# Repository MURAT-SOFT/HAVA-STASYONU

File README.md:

HAVA İSTASYON CİHAZI  HG-1,HG-2,HG-3,HG-4,HG-4İ VE B (V.1.2)
1.TASARIM SOLIDWORKS 2018
2.DONANIM TASARIMI : DIPTRACE VEYA AUTODESK EAGLE v.2024
3.YAZILIM: CCS-C C DERLEYİCİ v.5.11 VE STM32 CUBE IDE 
--------------------------------------------------------
KULLANILAN SENSÖRLER:
1.BOSCH BME280
2.DHT22 VEYA DS18B20 VE LM335,TC77
3.ANAKART PIC16F877A,PIC18F452,PIC18F4550,STM32103CBT6,STM32F407ZGT6,MSP430 VE ARDUINO
4.VOLTAJ REGÜLATÖR + TRAFO: 220v-> 12v 
5.EKRAN 1.ST7735 1.8/ST7789 2.4 INÇ VEYA LCD 16x2 
--------------------------------------------------------

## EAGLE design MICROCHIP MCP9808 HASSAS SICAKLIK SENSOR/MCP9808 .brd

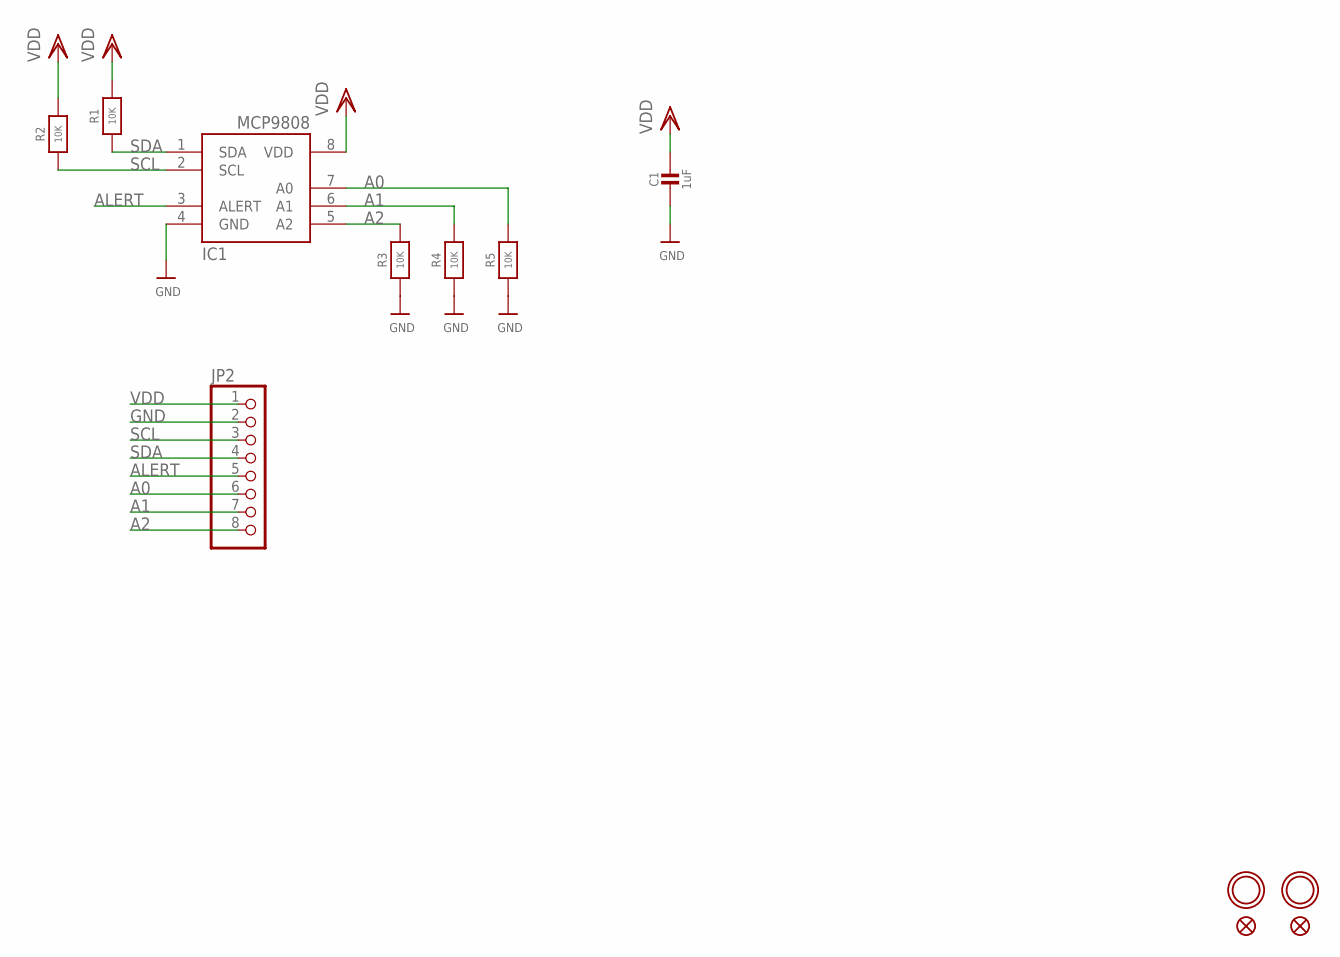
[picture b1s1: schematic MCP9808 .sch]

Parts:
C1: 1uF; _0805MP
FID1, FID2: FIDUCIAL""; FIDUCIAL_1MM
IC1: MCP9808-E/MS; MSOP8_0.65MM
JP2: HEADER-1X870MIL; 1X08_ROUND_70
R1, R2, R3, R4, R5: 10K; 0805-NO
U$3, U$5: MOUNTINGHOLE2.5; MOUNTINGHOLE_2.5_PLATED

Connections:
A0: IC1.7 (A0), JP2.6, R5.2
A1: IC1.6 (A1), JP2.7, R4.2
A2: IC1.5 (A2), JP2.8, R3.2
ALERT: IC1.3 (ALERT), JP2.5
GND: C1.2, IC1.4 (GND), JP2.2, R3.1, R4.1, R5.1
SCL: IC1.2 (SCL), JP2.3, R2.1
SDA: IC1.1 (SDA), JP2.4, R1.1
VDD: C1.1, IC1.8 (VDD), JP2.1, R1.2, R2.2

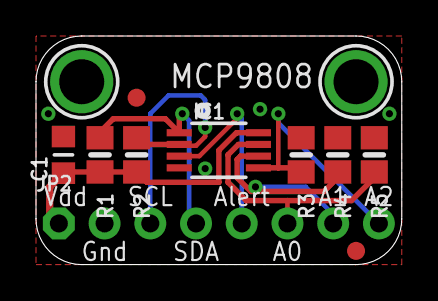
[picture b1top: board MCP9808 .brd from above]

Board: 2 copper layers, 20.3 x 12.7 mm, 12 parts (0 on the bottom side), 8 nets.

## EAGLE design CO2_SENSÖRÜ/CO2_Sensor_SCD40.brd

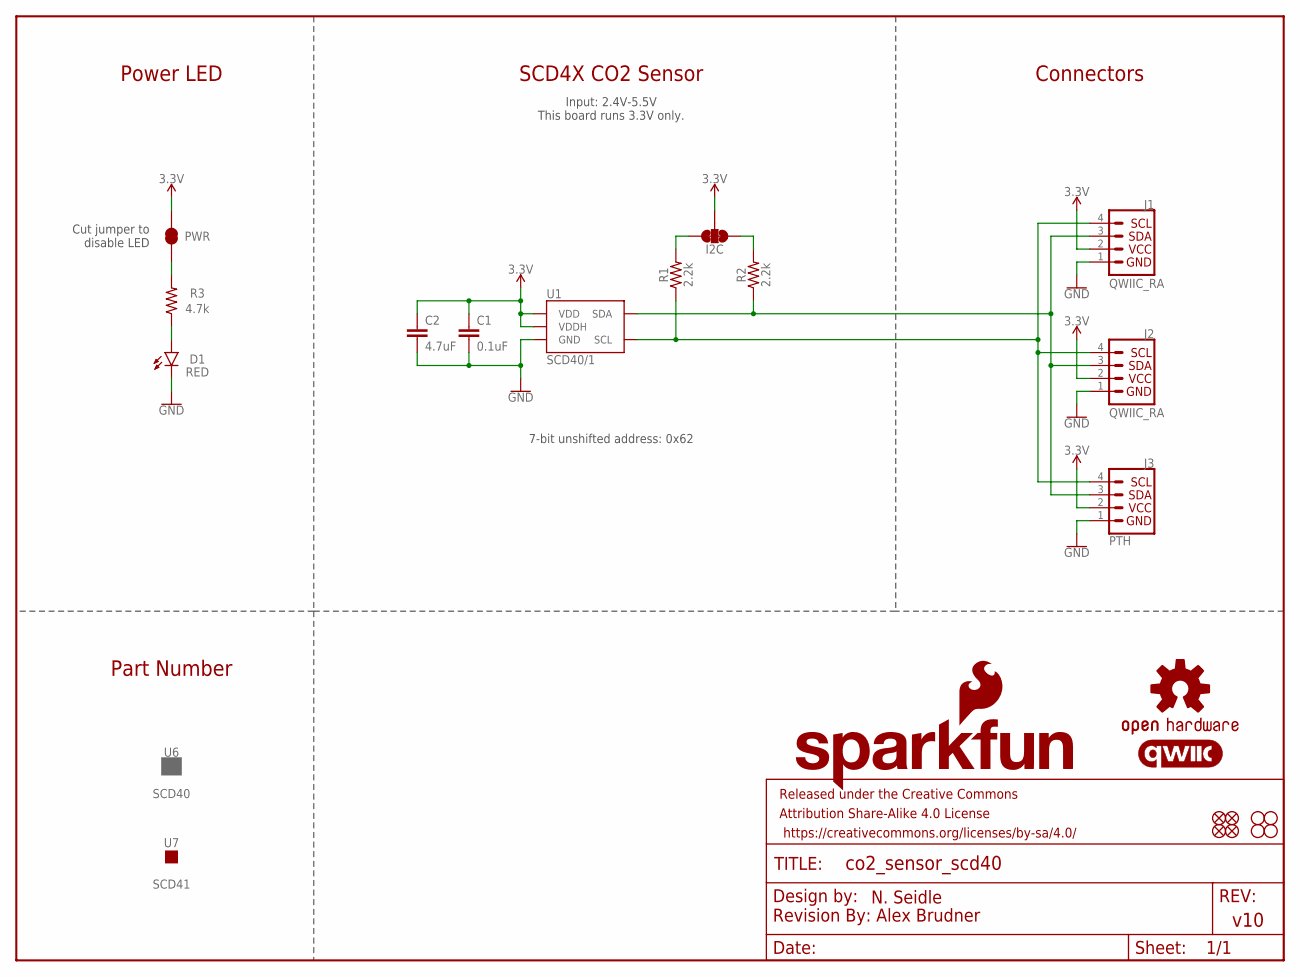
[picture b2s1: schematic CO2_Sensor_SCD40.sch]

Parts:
C1: 0.1uF; 0603
C2: 4.7uF; 0603
D1: RED; LED-0603
FD1, FD2, FD3, FD4: FIDUCIALUFIDUCIAL; FIDUCIAL-MICRO
FRAME1: FRAME-LETTER; CREATIVE_COMMONS
H1, H2, H3, H4: STAND-OFF
I2C: I2C; SMT-JUMPER_3_2-NC_TRACE_SILK
J1, J2: QWIIC_RA; JST04_1MM_RA
J3: PTH; 1X04_NO_SILK
LOGO1: QWIIC_LOGO_CONNECTOR; QWIIC_5.5MM
LOGO2: OSHW-LOGOS; OSHW-LOGO-S
LOGO3: SFE_LOGO_NAME_FLAMEBLANK; BLANK
PWR: PWR; SMT-JUMPER_2_NC_TRACE_SILK
R1, R2: 2.2k; 0603
R3: 4.7k; 0603
U1: SCD40/1; SCD4X
U6: SCD40; PRODUCT_IDENT_PASTE_NO-SILK
U7: SCD41; PRODUCT_IDENT_NO_NO-SILK

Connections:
3.3V: C1.1, C2.1, I2C.2, J1.2, J2.2, J3.2, PWR.2, U1.7 (VDD), U1.19 (VDDH)
GND: C1.2, C2.2, D1.C, J1.1, J2.1, J3.1, U1.6 (GND), U1.20 (GND), U1.CP (GND)
unnamed: I2C.1, R2.2
unnamed: I2C.3, R1.2
unnamed: PWR.1, R3.2
unnamed: D1.A, R3.1
SCL: J1.4, J2.4, J3.4, R1.1, U1.9 (SCL)
SDA: J1.3, J2.3, J3.3, R2.1, U1.10 (SDA)

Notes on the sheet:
Cut jumper to disable LED
SCD4X CO2 Sensor
Power LED
Connectors
Part Number
Input: 2.4V-5.5V This board runs 3.3V only.
7-bit unshifted address: 0x62

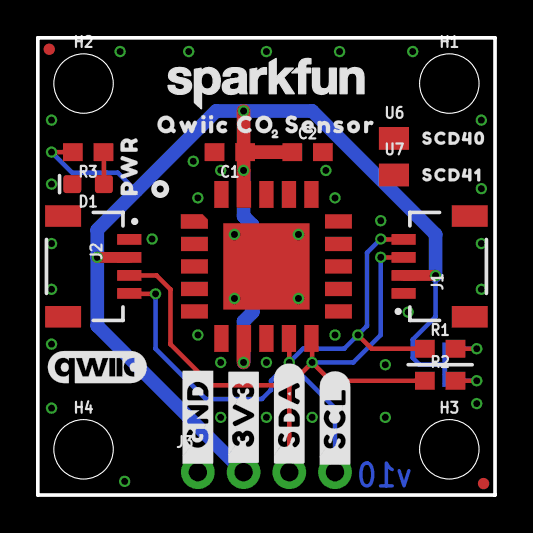
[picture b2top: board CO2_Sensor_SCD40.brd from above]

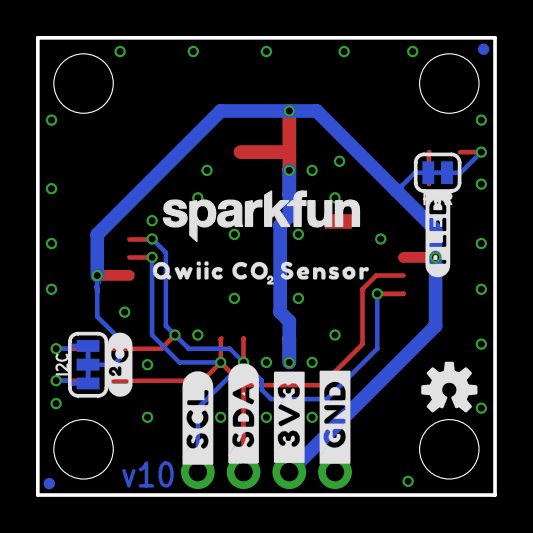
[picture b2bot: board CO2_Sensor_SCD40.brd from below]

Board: 2 copper layers, 25.4 x 25.4 mm, 49 parts (16 on the bottom side), 8 nets.

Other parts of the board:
U$1, U$18: #_GND#14
U$2, U$19: #_3V3#15
U$3, U$20: #_SDA#15
U$4, U$21: #_SCL#16
U$5, U$12: SFE_LOGO_NAME_.1
U$6: SCD414140404021
U$7: SCD40414140404022
U$8, U$13: QWIIC_CO0
U$9, U$14: SENSOR0
U$10, U$15: 20
U$11: SFE_LOGO_FLAME_STOP_.1
U$16: #PLED#21
U$17: #I�C#0
U$22: ORDERING_INSTRUCTIONS
U$23: PWR0

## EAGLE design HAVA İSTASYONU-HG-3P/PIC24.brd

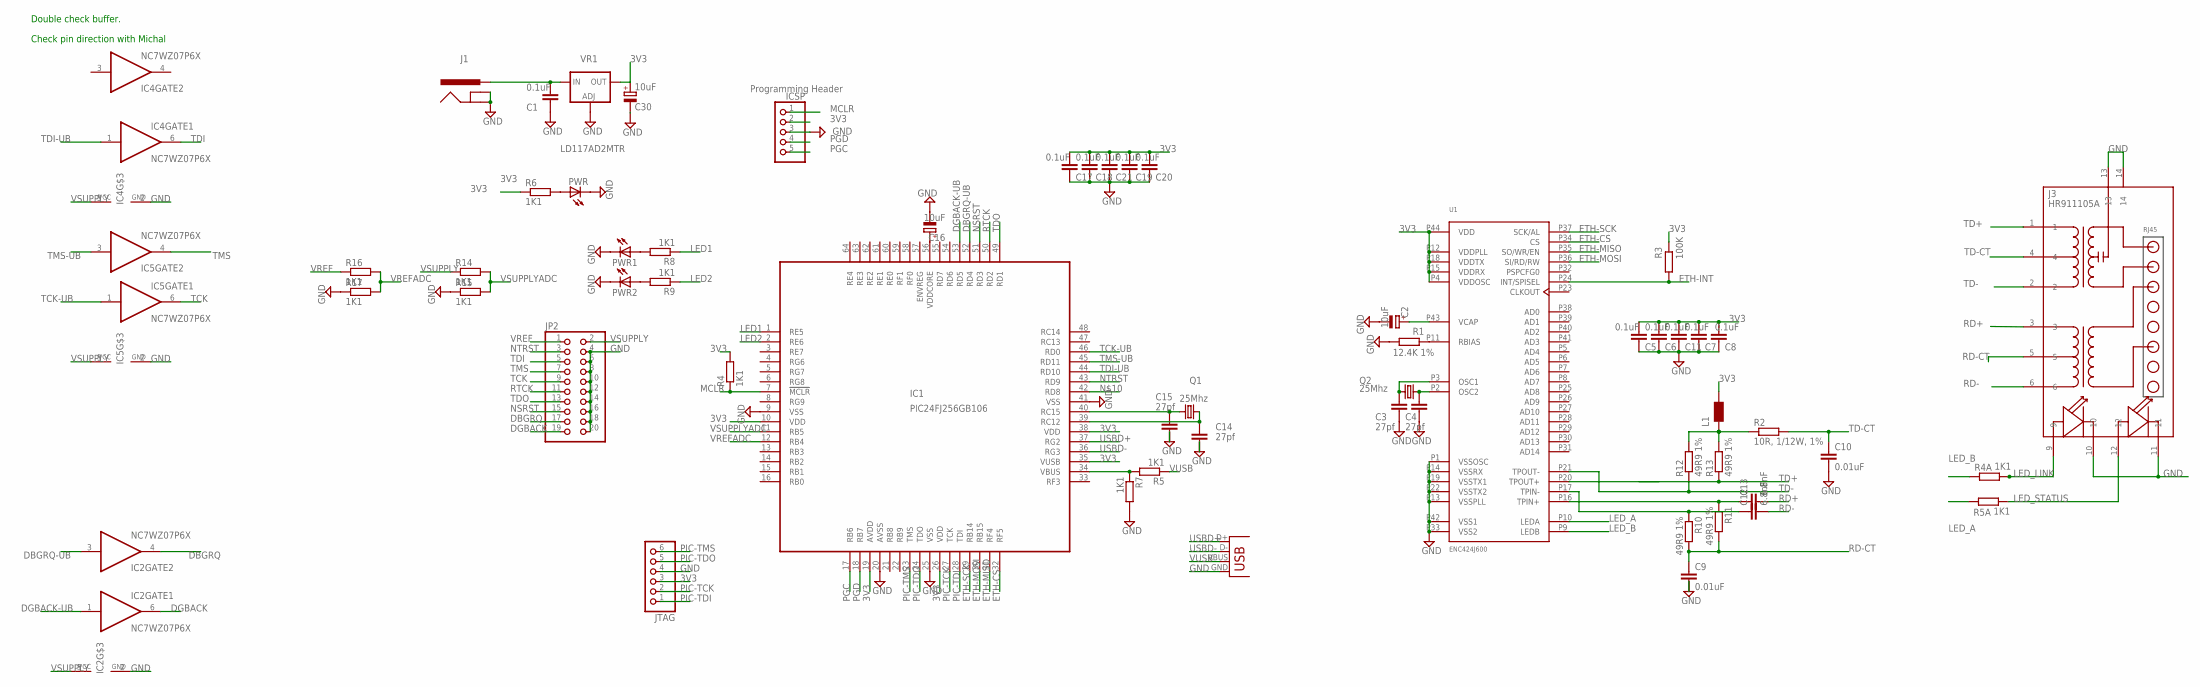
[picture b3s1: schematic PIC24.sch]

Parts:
C1, C5, C6, C7, C8, C11, C17, C18, C19, C20, C21: 0.1uF; C0603
C2, C16, C30: 10uF; SMC_A
C3, C4, C14, C15: 27pf; C0603
C9, C10: 0.01uF; C0603
C12, C13: 6.8nF; C0603
IC1: PIC24FJ256GB106; TQFP64-10X10
IC2, IC4, IC5: NC7WZ07P6X; SC70-6
ICSP: PINHD-1X5; 1X05
J1: POWER_JACKSMD; POWER_JACK_SMD
J3: HR911105A
JP2: PINHD-2X10; 2X10
JTAG: PINHD-1X6; 1X06
L1: WE-KIL_0805; WE-KI_0805_B
PWR, PWR1, PWR2: LEDCHIPLED_0603; CHIPLED_0603
Q1, Q2: 25Mhz; HC49UP
R1: 12.4K 1%; R0603
R2: 10R, 1/12W, 1%; R0603
R3: 100K; R0603
R4, R4A, R5, R5A, R6, R7, R8, R9, R14, R15, R16, R17: 1K1; R0603
R10, R11, R12, R13: 49R9 1%; R0603
U1: ENC424J600; TQFP44
VR1: LD117AD2MTR; D2PACK
X2: USBSMD; USB-MINIB

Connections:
3V3: C5.1, C6.1, C7.1, C8.1, C11.1, C17.1, C18.1, C19.1, C20.1, C21.1, C30.+, IC1.10 (VDD), IC1.19 (AVDD), IC1.26 (VDD), IC1.35 (VUSB), IC1.38 (VDD), ICSP.2, JTAG.3, L1.1 (2), R3.1, R4.2, R6.1, U1.P4 (VDDOSC), U1.P12 (VDDPLL), U1.P15 (VDDRX), U1.P18 (VDDTX), U1.P44 (VDD), VR1.2 (OUT)
CCT: L1.2 (1), R2.1, R12.2, R13.2
DBGRQ: IC2.4 (O), JP2.17
DBGRQ-UB: IC1.52 (RD4), IC2.3 (I)
DGBACK: IC2.6 (O), JP2.19
DGBACK-UB: IC1.53 (RD5), IC2.1 (I)
DSFGDF: C12.1, R10.1, U1.P17 (TPIN-)
DSGDFSG: C13.1, R11.1, U1.P16 (TPIN+)
ETH-CS: IC1.32 (RF5), U1.P34 (CS)
ETH-INT: R3.2, U1.P24 (INT/SPISEL)
ETH-MISO: IC1.31 (RF4), U1.P35 (SO/WR/EN)
ETH-MOSI: IC1.30 (RB15), U1.P36 (SI/RD/RW)
ETH-SCK: IC1.29 (RB14), U1.P37 (SCK/AL)
GND: C1.2, C2.-, C3.2, C4.2, C5.2, C6.2, C7.2, C8.2, C9.2, C10.2, C11.2, C14.2, C15.2, C16.-, C17.2, C18.2, C19.2, C20.2, C21.2, C30.-, IC1.9 (VSS), IC1.20 (AVSS), IC1.25 (VSS), IC1.41 (VSS), IC2.2 (GND), IC4.2 (GND), IC5.2 (GND), ICSP.3, J1.GND (GNDBREAK), J1.P$4 (GND), J3.10, J3.11, J3.13, J3.14, JP2.4, JP2.6, JP2.8, JP2.10, JP2.12, JP2.14, JP2.16, JP2.18, JP2.20, JTAG.4, PWR.C, PWR1.C, PWR2.C, R1.2, R7.2, R15.1, R17.1, U1.P1 (VSSOSC), U1.P13 (VSSPLL), U1.P14 (VSSRX), U1.P19 (VSSTX1), U1.P22 (VSSTX2), U1.P33 (VSS2), U1.P42 (VSS1), VR1.1 (ADJ), X2.GND
LED1: IC1.1 (RE5), R8.1
LED2: IC1.2 (RE6), R9.1
LED_A: R5A.1, U1.P10 (LEDA)
LED_B: R4A.1, U1.P9 (LEDB)
LED_LINK: J3.9, R4A.2
LED_STATUS: J3.12, R5A.2
MCLR: IC1.7 (!MCLR), ICSP.1, R4.1
unnamed: C2.+, U1.P43 (VCAP)
unnamed: R1.1, U1.P11 (RBIAS)
unnamed: C15.1, IC1.40 (RC15), Q1.1
unnamed: C3.1, Q2.1, U1.P3 (OSC1)
unnamed: C14.1, IC1.39 (RC12), Q1.2
unnamed: PWR1.A, R8.2
unnamed: PWR2.A, R9.2
unnamed: C4.1, Q2.2, U1.P2 (OSC2)
unnamed: C16.+, IC1.56 (VDDCORE)
unnamed: IC1.34 (VBUS), R5.2, R7.1
unnamed: PWR.A, R6.2
NSRST: IC1.51 (RD3), JP2.15
NTRST: IC1.43 (RD9), JP2.3
PGC: IC1.17 (RB6), ICSP.5
PGD: IC1.18 (RB7), ICSP.4
PIC-TCK: IC1.27 (TCK), JTAG.2
PIC-TDI: IC1.28 (TDI), JTAG.1
PIC-TDO: IC1.24 (TDO), JTAG.5
PIC-TMS: IC1.23 (TMS), JTAG.6
RD+: C13.2, J3.3
RD-: C12.2, J3.6
RD-CT: C9.1, J3.5, R10.2, R11.2
RTCK: IC1.50 (RD2), JP2.11
TCK: IC5.6 (O), JP2.9
TCK-UB: IC1.46 (RD0), IC5.1 (I)
TD+: J3.1, R13.1, U1.P20 (TPOUT+)
TD-: J3.2, R12.1, U1.P21 (TPOUT-)
TD-CT: C10.1, J3.4, R2.2
TDI: IC4.6 (O), JP2.5
TDI-UB: IC1.44 (RD10), IC4.1 (I)
TDO: IC1.49 (RD1), JP2.13
TMS: IC5.4 (O), JP2.7
TMS-UB: IC1.45 (RD11), IC5.3 (I)
USBD+: IC1.37 (RG2), X2.D+
USBD-: IC1.36 (RG3), X2.D-
VBAT: C1.1, J1.VIN0 (PWR), VR1.3 (IN)
VREF: JP2.1, R16.1
VREFADC: IC1.12 (RB4), R16.2, R17.2
VSUPPLY: IC2.5 (VCC), IC4.5 (VCC), IC5.5 (VCC), JP2.2, R14.1
VSUPPLYADC: IC1.11 (RB5), R14.2, R15.2
VUSB: R5.1, X2.VBUS

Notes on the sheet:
Programming Header
Check pin direction with Michal
Double check buffer.

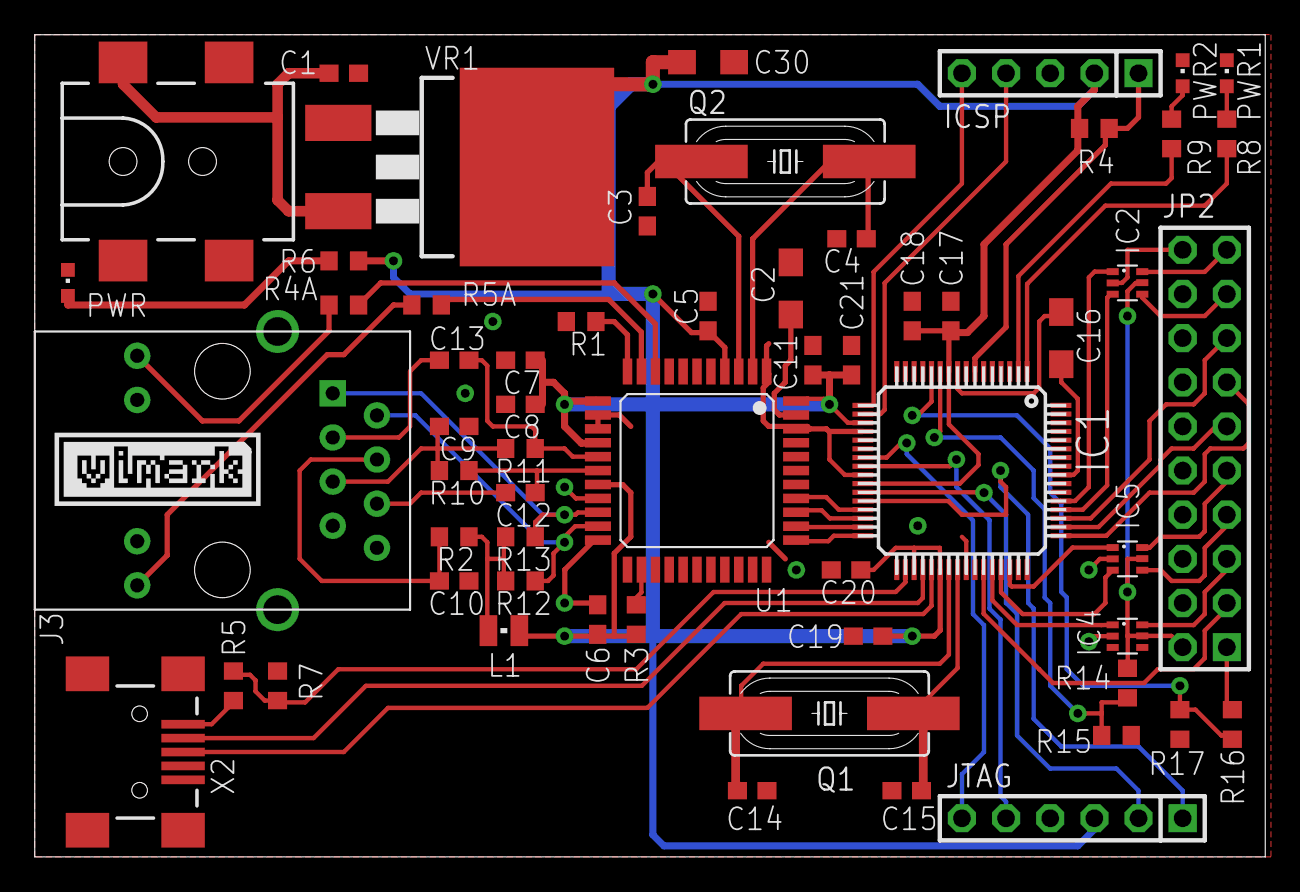
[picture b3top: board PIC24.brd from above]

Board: 2 copper layers, 70.8 x 47.3 mm, 60 parts (0 on the bottom side), 62 nets.

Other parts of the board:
U$1: VIMARK_LOGO

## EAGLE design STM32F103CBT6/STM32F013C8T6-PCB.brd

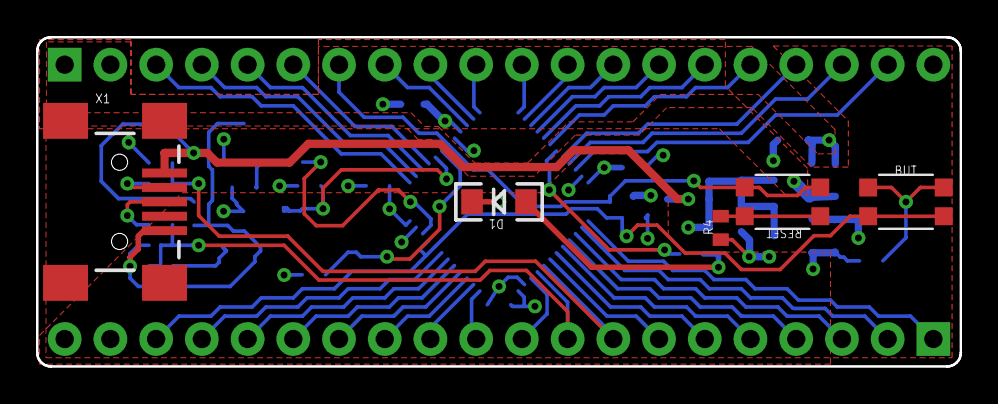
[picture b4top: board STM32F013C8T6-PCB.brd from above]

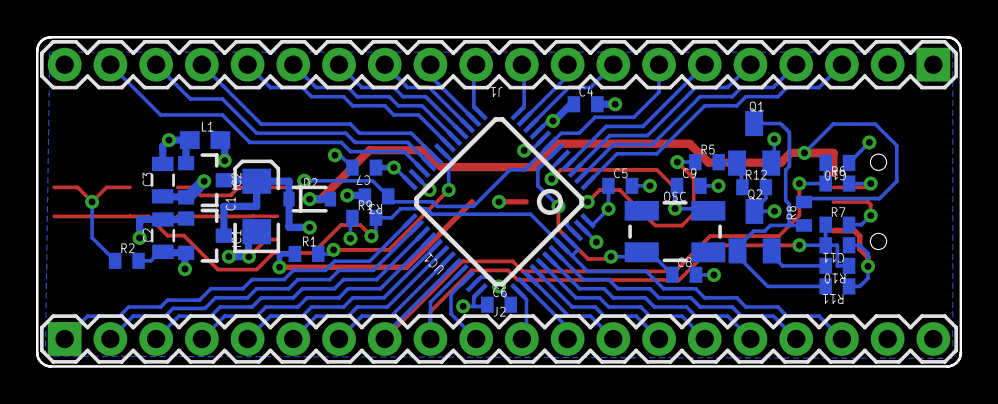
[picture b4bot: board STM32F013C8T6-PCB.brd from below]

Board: 2 copper layers, 51.3 x 18.3 mm, 37 parts (32 on the bottom side), 52 nets.

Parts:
BUT: KMR211GLFS; PUSHBUTTON-KMR241GLFS
C1: 100uF; EIA3216
C2, C3: 10uF; 0805
C4, C5, C6, C7: 1uF; C0402
C8, C9: 18pF; C0402
C10, C11: 47pF; C0402
D1: Blue; LED-1206
D2: SOD-323
IC1, IC2: MCP1703T-3302E/CB; SOT23
J1, J2: M20; 1X20
L1: ferrite bead; 0603
OSC: 8MHz; CRYSTAL-SMD-5X3
Q1, Q2: NPN-BJT; SOT23_Q1
R1, R2, R5: 1k; C0402
R3, R8, R9: 10k; C0402
R4: 1k; C0402_R4
R6, R7: 22; C0402
R10: 1.5k; C0402
R11: 36k; C0402
R12: 47k; C0402
RESET: KMR211GLFS; PUSHBUTTON-KMR241GLFS
UC1: STM32F103CBT6; LQFP48
X1: USB-MINIB

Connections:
0: J1.19, UC1.22
1: J1.18, UC1.21
2: J1.17, UC1.20
3: J1.16, UC1.18
4: J1.15, UC1.17
5: J1.14, UC1.16
6: J1.13, UC1.15
7: J1.12, UC1.14
8: J1.11, UC1.13
9: J1.10, UC1.12
10: J1.9, UC1.11
11: J1.8, UC1.10
12: J1.6, UC1.4
13: J1.5, UC1.3
14: J1.4, UC1.2
15: J2.17, UC1.43
16: J2.16, UC1.42
17: J2.15, UC1.41
18: J2.14, UC1.40
19: J2.13, UC1.39
20: J2.12, UC1.38
21: J2.11, UC1.37
22: J2.10, UC1.34
23_USBDP: C11.2, J2.9, R7.1, R10.1, UC1.33
24_USBDM: C10.2, J2.8, R6.1, UC1.32
25: J2.7, UC1.31
26: J2.6, UC1.30
27: J2.5, UC1.29
28: J2.4, UC1.28
29: J2.3, UC1.27
30: J2.2, UC1.26
31: J2.1, UC1.25
32: BUT.P$2, BUT.P$4, J2.18, R9.2, UC1.44, UC1.45
33: R1.2, UC1.19
+5V/2: D2.2, R8.2, X1.VBUS
AV+: C3.1, C4.1, IC2.2, J1.1, UC1.9
AV-: C3.2, C4.2, IC2.1, J1.2, L1.1, UC1.8
DGND: C1.C, C2.2, C5.2, C6.2, C7.2, C8.2, C9.2, C10.1, C11.1, D1.C, IC1.1, J2.19, L1.2, Q1.2, R4.1, R9.1, R11.1, UC1.23, UC1.35, UC1.47, X1.GND
DISC: R5.1, UC1.46
unnamed: D1.A, R1.1
unnamed: R4.2, RESET.P$1, RESET.P$3
unnamed: Q2.2, R10.2
unnamed: R6.2, X1.D-
unnamed: R7.2, X1.D+
unnamed: Q1.3, Q2.1, R8.1, R11.2
unnamed: Q1.1, R5.2, R12.1
OSC_IN: C9.1, OSC.3, UC1.5
OSC_OUT: C8.1, OSC.1, UC1.6
RESET: J1.7, R3.1, RESET.P$2, RESET.P$4, UC1.7
VBAT: J1.3, UC1.1
VCC: C2.1, C5.1, C6.1, C7.1, IC1.2, J2.20, Q2.3, R2.2, R3.2, R12.2, UC1.24, UC1.36, UC1.48
VIN: C1.A, D2.1, IC1.3, IC2.3, J1.20

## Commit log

2024-12-01 HAVA İSTASYONU microchip pic16f877a MCU v.1.02
    8-BIT HAVA İSTASYON ÖLÇÜM CİHAZI (CCS-C DERLEYİCİ)
2024-12-01 OKU.md
2024-12-03 PIC16F877A OLED TEST
2024-12-04 MICROCHIP PIC16F877A HAVA İSTASYONU KART
2024-12-04 HAVA İSTASYONU HG-1 (REV.A)
    1.SITRONIX ST7735 LCD
    2.PIC16F877A MCU
    3.BOSCH BME280 SENSOR
    4.LM7805 REGÜLATÖR
    CCS_C DERLEYİCİ YAZILIMI VE ARDUNIO YAZLIMI.
    MURAT IRKAN 2022
2024-12-04 HAVA İSTASYON CİHAZI HG-1
    MURAT IRKAN 2021
2024-12-04 HAVA İSTASYONU DEMO PCB(DIPTRACE 2024)
2024-12-04 HG-1 PCB DIPTRACE v.2024
2024-12-04 HAVA İSTASYONU PCB REV.B (PROGRAM DIPTRACE 2024)
2024-12-05 SOLIDWORKS 2018 3D-TASARIM(HAVA İSTASYON HG-1)
2024-12-05 HG-1 HAVA İSTASYONU RESİM-1
2024-12-05 PIC16F877A MCU PCB MONTAJ
2024-12-05 HAVA İSTASYONU HG-1 PIC16F877A KART MONTAJ-1
2024-12-05 HAVA İSTASYON_MONTAJ_SENSORLÜ
2024-12-06 HAVA İSTASYON 3D-TASARIM TEK PARÇALI
2024-12-06 HG-1 ŞASE_SİYAH
    PLASTİK
2024-12-06 HG-1 SİYAH_ŞASE RESİM
2024-12-08 MICROCHIP PIC16F1938_(HAVA İSTASYON KARTI REV.B)
    MURAT IRKAN HAVA İSTASYON CİHAZI PIC16F1938 DEVRE + PCB
2024-12-08 OKU_BENİ.md
2024-12-08 pıc16f1938_teknik_döküman
2024-12-08 HAVA İSTASYONU_3D_TASARIM_DOSYALAR
    SOLIDWORKS ENDÜSTRYEL TASARIM PROGRAMI 2018
2024-12-08 SICAKLIK SENSÖRLERİ(TEKNİK DÖKÜMANLARI)
2024-12-08 PIC18F4550 DEVRE_ŞEMA
2024-12-08 MCP9700 TERMİSTÖR
2024-12-08 GÖVDE_METAL_GÜMÜŞ
2024-12-08 GÖVDE_RESİM_METAL
2024-12-08 PIC16F1938_PCB_REV.A(DIPTRACE PROGRAMI v.2024)
2024-12-08 HG-2 HAVA İSTASYON PIC16F1938 MCU_KART
    1.BOSCH BME280 SENSÖR
    2.SITRONIX ST7735S 1.8INÇ TFT-LCD EKRAN
    3.PIC16F1938 MCU KART-PCB
2024-12-08 HAVA İSTASYONU PIC16F877A VE DS18B20 SENSOR(CCS-C)
2024-12-08 ARDUINO_HAVA_İSTASYONU_YAZLIMI +3D-TASARIM
    BOSCH SENSOR BME280 HARİÇ.
2024-12-08 PIC16F877A_LM35DZ_SENSOR_PCB
2024-12-08 PIC16F877A_LM35_SENSOR_PCB
2024-12-08 PIC16F877A_REV.D
2024-12-08 PIC16F877A_REV_D
2024-12-08 PIC16F877A_KART_3D_REV.E
    3D STEP DOSYASI(SOLIDWORKS 2018)
2024-12-08 HAVA_İSTASYON_3D_TASARIM(REV.E)
    SOLIDWORKS 2018
    ----------------------,
    MURAT IRKAN 2024/12
2024-12-08 HAVA_İSTASYON_ŞASE_VİDALI
2024-12-08 HAVA_İSTASYON_AHŞAP_MODEL
    1.ANAKART_PIC16F877A_LM60-LM35_BOSCH_BME280 SENSÖRLERİ
    2.EKRAN:SITRONIX ST7735S
2024-12-09 HAVA İSTASYON CİHAZI HG-1P MURAT IRKAN 2024
    1. EAGLE VEYA DIPTRACE v.2024 DEVRE ŞEMA + PCB
    2.3D TASARIMLARI:SOLIDWORKS 2018
    3.CİHAZ YAZILIMI :CCS-C DERLEYİCİ PIC16F877A / PIC18F4550 VEYA STM32F407ZGT6 ARM M4 CORTEX CPU
2024-12-09 HAVA_İSTASYONU_LIPO_PİL(SOLIDWORKS 2018)
    LIPO PİL EKLENDİ 1350 mA/h:
    ---------------------------------
2024-12-09 HAVA İSTASYONU(LI-PO_PİL EKLENDİ)
    1.ANAKART PIC16F877A VE DEVRE ŞEMASI + PCB-DIPTRACE VEYA EAGLE
    2.SOLIDWORKS 2018 3D TASARIM PROGRAMI
    3.CCS-C YAZILIMI.
2024-12-09 HAVA İSTASYONU rev.e (MURAT IRKAN 2024-11)
    1.3D TASARIM:SOLIDWORKS 2018
    2.DEVRE TASARIMI:DIPTRACE 2024 VEYA AUTODESK EAGLE
    3.YAZILIM:CCS-C C DERLEYİCİ v.5.11
    MURAT IRKAN 2024
2024-12-10 HAVA İSTASYONU HG-2
    1-PIC16F877A-PIC16F887
    2.SOLIDWORKS LCD 16x2 MİNİ TASARIM
    3.YAZILIM:CCS-C DERLEYİCİ v.5.11
2024-12-11 ARDUINO_UNO_HAVA_İSTASYON(3D TASARIM SOLIDWORKS)
    1.PROTOTİP 1A
2024-12-11 ARDUINO UNO HAVA İSTASYON RESİM-1
2024-12-11 ARDUINO HAVA İSTASYONU + 3.7v LI-PO PİL_3D MODEL
2024-12-11 ARDUINO HAVA İSTASYONU-Lİ-PO PİL + BOSCH BME280
    SOLIDWORKS 2018 TASARIM
2024-12-14 PIC16F887 HAVA İSTASYONU DHT22 KODLARI ( CCS-C )
2024-12-14 HAVA İSTASYON CİHAZI REV.F
    1.DIPTRACE PROGRAMI DEVRE + BASKI DEVRE(PCB) 3 VERSİYON
    2.SOLIDWORKS 2018 ŞASE TASARIMI 2 ADET
    3.CCS-C C PROGRAMLAMA DİLİ VE DERLEYİCİ.
    MURAT IRKAN 2024/12
2024-12-18 STM32F407ZGT6 ARM HAVA İSTASYONU VE KAYIT CİHAZI
    1.STM32F407ZGT6 ARM CORTEX ANAKART(USB VE MİKRO-SD KART)
    SICAKLIK,BASINÇ,NEM VE HAVA KALİTESİ ÖLÇÜMÜ VE KAYIT.
    2.SOLIDWORKS 2018 3D TASARIM MODELİ (STEP DOSYASI)
2024-12-18 OKUYUN.md
2024-12-18 PIC16F887 DHT22 HAVA İSTASYONU
2024-12-19 HAVA İSTASYON HG-3 (REV.A)
    1.MICROCHIP PIC16F877A VEYA PIC16F887-MCU
    BOSCH BME280 VEYA DHT22 SENSÖR
    2.SOLIDWORKS 2018
    3.DIPTRACE 2024 DEVRE TASARIM
2024-12-19 HG-3 3D TASARIM RESİMLER
2024-12-19 HAVA İSTASYON TASARIM HG-2(ARKA KABLO GİRİŞ)
    SOLIDWORKS 2018 -19-12-2024
2024-12-22 HAVA İSTASYONU (TASARIM,YAZILIM VE DONANIM MURAT IRKAN)
    HAVA İSTASYON CİHAZI HG-1P REV.A
2024-12-22 BİLGİ.md
2024-12-22 HAVA İSTASYON CİHAZI HG-1P (YUVARLANMIŞ ŞASE)
2024-12-22 Create BİLGİ DÖKÜMANLARI
2024-12-22 BOSCH BME280 SENSÖR
2024-12-22 MICROCHIP MCP9700A SENSÖR
2024-12-22 TEXAS INSTRUMENTS LM35 SENSÖR
2024-12-22 AOSONG DHT22 SENSÖR
2024-12-23 HAVA İSTASYON CİHAZI HG-1S(v.1.02)
    1.SOLIDWORKS 2018 3D ŞASE TASARIM VE MONTAJ
    2.DIPTRACE 2024 DEVRE DİZAYN PROGRAMI
    3.CCS.C v.5.11 C DERLEYİCİ VE IDE
    MURAT IRKAN 2024
2024-12-23 HAVA İSTASYON CİHAZI HG-1S (TFT EKRAN ST7735/R/S)
    RENKLİ TFT-LCD EKRAN 1.8 VEYA 2.4 INÇ ST7735-ST7789
2024-12-26 Create RP2040
2024-12-26 HAVA İSTASYONU RASPBERRY PI 2040
2024-12-26 HAVA İSTASYONU HG-3P PIC24 16-BIT MCU
    1.AUTODESK EAGLE DEVRE ŞEMA VE PCB
    2.PIC24FJ256GB106 16-BIT MCU DATASHHET(TEKNİK DÖKÜMANI)
2024-12-26 PIC24FJ256GB106 16-BIT MCU => 3D PCB DOSYASI
2024-12-29 HAVA İSTASYONU_ŞEMA(PIC18F4550-USB)
2024-12-30 HAVA İSTASYONU HG-2
    1.PIC18F452 MCU DEVRE ŞEMASI(DIPTRACE 2024)
    2.SOLIDWORKS 2018 ŞASE TASARIM
    3.LCD 16x2 + BOSCH BME280 SENSÖR + DHT22 SENSÖR + 220v ADAPTÖR
2024-12-30 HAVA İSTASYONU HG-2P (30/12/2024)
    1.DIPTRACE DEVRE ŞEMASI(PIC18F452)
    2.SOLIDWORKS 2018 3D ŞASE TASARIMI
    3.CCS-C C DERLEYİCİ...
2024-12-31 HAVA İSTASYON -KABLOLU
2025-01-03 HAVA İSTASYONU HG-2
    TASARIM,DONANIM,YAZILIM: MURAT IRKAN 2022/06
    1.SOLIDWORKS 2018
    2.DIPTRACE 2024
    3.CCS-C C DERLEYİCİ
2025-01-03 HAVA İSTASYONU PIC16F877A,PIC18F452,PIC24FJ256GB206
    1.TASARIM: SOLIDWORKS 2018
    2.DONANIM:DIPTRACE VEYA EAGLE
    3.YAZILIM: CCS-C DERLEYİCİ v.5.11
    MURAT IRKAN 2023
2025-01-03 HAVA İSTASYONU HG-2 ATMEGA16 MCU
    DIPTRACE 2024
2025-01-03 ATMEGA 16 TEKNİK DÖKÜMAN(DATASHEET)
2025-01-03 KARBONDIOKSIT SENSOR
2025-01-03 PIC18F2550
2025-01-05 LM135,LM335 SICAKLIK SENSÖR DÖKÜMANI
2025-01-06 MICROCHIP PIC18F4550 HAVA İSTASYONU DEVRESİ
2025-01-06 SCD40 KARBONDIOKSİT ÖLÇÜM SENSÖRÜ DEVRE+PCB
2025-01-06 HAVA İSTASYONU VE HAVA KALİTESİ CİHAZI(HG-2 REV.A)
    1.SENSORLER:BOSCH BME280 + DHT22 + LM135(LM335)+ MCP9700A/B + SCD40
2025-01-06 HAVA İSTASYONU HG-2 (CO2 SENSÖR + METAL KASA )
    HG-2 HAVA İSTASYONU VE HAVA KALİTESİ ÖLÇÜM CİHAZI REV.B
    06/01/2024
    -------------------------------------------------------------------------------
2025-01-06 HG-2 ARKA KESİT TASARIMI
2025-01-06 SITRONIX ST7735 2.4INÇ TFT LCD RENKLİ EKRAN
2025-01-06 IŞIK ÖLÇÜM SENSÖRÜ
2025-01-07 HG-2 PIC18F452 PCB(BASKI DEVRE) REV.A
2025-01-07 HAVA İSTASYONU HG-2 PCB-BASKI DEVRE (REV.A)
2025-01-07 ADAFRUIT BOSCH BME280 SENSÖR MÖDÜLÜ
2025-01-09 HAVA İSTASYONU HG-2 (GÜNCELLEME PIC18F452 PCB)
    1-ŞASE TASARIM:SOLIDWORKS 2018
    2.DONANIM TASARIM: DIPTRACE 2024
    3.YAZILIM: CCS-C (v.5.11) MURAT IRKAN v.1.2
2025-01-09 HAVA İSTASYON CİHAZI HG-2 (PIC16877A/PIC18F452)
    1. 3D TASARIM : SOLIDWORKS 2018 MURAT IRKAN
    2. DONANIM TASARIM: DIPTRACE 2024 MURAT IRKAN
    3. YAZILIM: CCS-C 5.11 DERLEYİCİ MURAT IRKAN
2025-01-09 HG-1 HAVA İSTASYONU
    1.SOLIDWORKS 2018: TASARIM
    2.DIPTRACE 2024- DONANIM TASARIMI
    3.CCS-C 5.11-YAZILIM
2025-01-09 HAVA İSTASYONU HG-3
    MCU:PIC24FJ256GB106 AUTODESK EAGLE DEVRE ŞEMA + PCB V.1.1
    ---------------------------------------------------------------------
2025-01-10 HG-2 HAVA İSTASYONU PIC16F877A PCB REV.C
2025-01-10 HAVA İSTASYON CİHAZI (HG-1 VE HG-2 ŞASE TASARIM)
    1.SOLIDWORKS 2018
2025-01-10 HAVA İSTASYONU HG-4 STM32F407ZGT6 ARM CORTEX M4
    AUTODESK EAGLE DEVRE + PCB TASARIM PROGRAMI.
    ------------------------------------------------------------
2025-01-10 HAVA İSTASYONU HG-4 STM32F103CBT6 DEVRE TASARIMI
    AUTODESK EAGLE
2025-01-10 CİHAZ_HAKKINDA.md
2025-01-11 STM32F103CBT6 ARM CORTEX HAVA İSTASYONU HG-4
    STM32F103CBT6 LCD 16x2 ARM KEIL 2024
2025-01-11 HAVA İSTASYON CİHAZI STM32-32_BIT ARM
    1.ANA KART : AUTODESK EAGLE : STM32F103CBT6 ARM CORTEX MPU
    2.TASARIM : SOLIDWORKS 2018
    3.YAZILIM : ARM KEIL 2024
2025-01-13 HAVA İSTASYON CİHAZI HG-4 STM32F103CBT6 REV.B
    HAVA İSTASYON CİHAZI HG-4- DIPTRACE 2024 PCB GÜNCELLEMESİ.
    STM32F103CBT6 ARM M3 MPU
2025-01-13 HAVA İSTASYONU HG-4İ
    İNTERNET HAVA İSTASYONU (STM32F407ZET6-100MBIT LAN)
2025-01-17 HG-4 REV.C HAVA İSTASYON CİHAZI
    DIPTRACE FREE VERSİYON 2024.
    MICROCHIP TC77 SENSÖR + DS1302 SAAT-TARİH CHİP PCB TASARIMI.
    HARİCİ BOSCH BME 280 VEYA DHT22
2025-01-17 HG-2 PIC18F452 PCB REV.C
    HARİCİ SENSÖRLER : BOSCH BME280 + DHT22
    DAHİLİ : TC77 + DS1302 SAAT/TARİH CHIP
2025-01-17 HAVA İSTASYONU TASARIM RESİMLERİ
2025-03-13 TMP118_NANO_SENSÖR
2025-03-13 BASINÇ ÖLÇÜM SENSÖR
2025-03-14 TMP117 SENSOR VE ARDUINO KOD+KÜTÜPHANE
2025-03-14 HAVA İSTASYONU ÖNDEN(MURAT IRKAN 2024/05)
    SOLIDWORK 2018 3D TASARIM
2025-03-14 STM32F107VCT6 ARM CORTEX M3 KONTROL ŞEMASI ( PDF )
    HAVA İSTASYONU STM32F107VCT6 ARM KONTROL KART
2025-03-14 STM32F401CCU6 ARM CORTEX M4 KART PDF DOSYA
2025-03-14 STM32F103C8T6 ARM CORTEX M3 KART
    MURAT IRKAN 2023/12
2025-03-14 STM32F103ZET6 ARM CORTEX M3 KART
2025-03-14 STM32F030F4P6 ARM CORTEX KART PDF
2025-03-14 STM32F103 TEST KODLARI HAVA İSTASYONU ARM KEIL IDE
2025-03-16 HAVA İSTASYONU HG-2 STM32F103 ARM CORTEX
    STM32 CUBE IDE
2025-03-16 STM32F103CBT6 ARM HAVA İSTASYONU HG-2 PCB
2025-03-16 HG-2 HAVA İSTASYONU TASARIM
2025-03-16 HAVA İSTASYONU HG-2 PIC16F1938 PCB
    DIPTRACE TASARIM PROGRAMI 2024
2025-03-16 HAVA İSTASYONU CCS-C DERLEYİCİ PIC18F46K22 MCU
2025-03-16 HG-2 PIC18F46K22 VE ST7789 LCD EKRAN 2.8 INÇ
2025-03-16 Create MSP430
2025-03-16 MSP430 16-BIT MCU DIPTARCE DEVRE ŞEMASI
2025-03-16 MICROCHIP 32-BIT
    PIC32MZ2048ECG144 MCU KONTROL KART AUTODESK EAGLE
2025-03-16 ESP32 KONTROL KART
2025-03-25 MICROCHIP PIC32 144 PIN KART
    AUTODESK EAGLE
2025-03-25 TI MSP430 16-BIT MCU DEVRE ŞEMASI DIPTRACE
    DEVRE ŞEMASI DIPTRACE PROGRAMI
2025-03-25 MSCP9808 HASSAS SICAKLIK SENSÖR DİZAYN
    AUTODESK EAGLE VEYA DIPTRACE
2025-03-26 SSD1306 1.3 INC OLED EKRAN
    SOLIDWORKS 2018
2025-03-26 PIC18F46K22 PROTEUS SIMULASYONU
2025-03-26 25-03-2025.md
2025-03-31 HAVA İSTASYON CİHAZI HG-2 PIC24 PCB
    REV.B 01/03/25
2025-04-01 DUMAN DETEKTÖRÜ DEVRE ŞEMA
2025-04-01 PIC24 DEVRE ŞEMASI + PCB
2025-04-04 PIC32MZ2048EF 32-BIT KART
    DIPTRACE 2024
2025-04-04 PIC32MZ2048EF TEKNİK DÖKÜMANI
    KONTROL -1
2025-04-04 5.5 V ÇIKIŞ 2 AMPER REGÜLATÖR
2025-04-04 MCP73812 ŞARŞ IC
    PDF
2025-06-22 STM32F103CBT6 ARM CORTEX M3 AUTODESK EAGLE
    MURAT IRKAN 2023-05 REV.A
    ---------------------------------
2025-06-23 HAVA İSTASYON CİHAZ- PIC32
    DIPTRACE DEVRE ŞEMASI
2025-06-23 ŞARJ DEVRESİ DÖKÜMANI
2025-06-23 STM32F103C8T6 DEVRE+ PCB HG-2 HAVA İSTASYONU
2025-06-23 STM32F103C8T6- V.1.1
2025-06-23 STM32F103C8T6 STM32CUBE IDE YAZILIMI
    MURAT IRKAN V.1.1
2025-06-23 STM32F405RET6 ARM CORTEX M4 HG-3 PDF DOSYA
2025-06-23 HAVA İSTASYONU VE WEB SERVER PIC18
2025-06-23 HAVA İSTASYONU WEB VERSİYONU PIC18
2025-06-23 HAVA İSTASYONU HG-4 STM32F407ZET6
    DIPTRACE DEVRE ŞEMASI V.1.1
    ----------------------------
2025-06-23 YANGIN ALARMI-ARDUINO UNO 3D MODEL
2025-07-06 HAVA İSTASYONU HG-2A
    1.YAZILIM : CCS-C DERLEYİCİ
    2.TASARIM MODELLEME: SOLIDWORKS 2018
    3.DEVRE TASARIM : DIPTRACE
2025-07-06 DUMAN DETEKTÖRÜ
2025-07-06 HG-2A PIC16F877A 3D MODEL + PCB KART
2025-07-06 BOSCH BME 280 PCB + DEVRE+ 3D MODEL
2025-07-06 DS18B20 SICAKLIK SENSÖR 3D MODELLERİ
2025-07-06 SITRONIX ST7735 1.8 INÇ LCD EKRAN 3D MODELİ
2025-07-06 USB SARJ KONTROL ÜNİTESİ (IC)

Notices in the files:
parts and their libraries:
SparkFun-Aesthetics: Licensing: Creative Commons ShareAlike 4.0 International - https://creativecommons.org/licenses/by-sa/4.0
SparkFun-Aesthetics: Released under the Creative Commons Attribution Share-Alike 4.0 License
SparkFun-Aesthetics: https://creativecommons.org/licenses/by-sa/4.0
